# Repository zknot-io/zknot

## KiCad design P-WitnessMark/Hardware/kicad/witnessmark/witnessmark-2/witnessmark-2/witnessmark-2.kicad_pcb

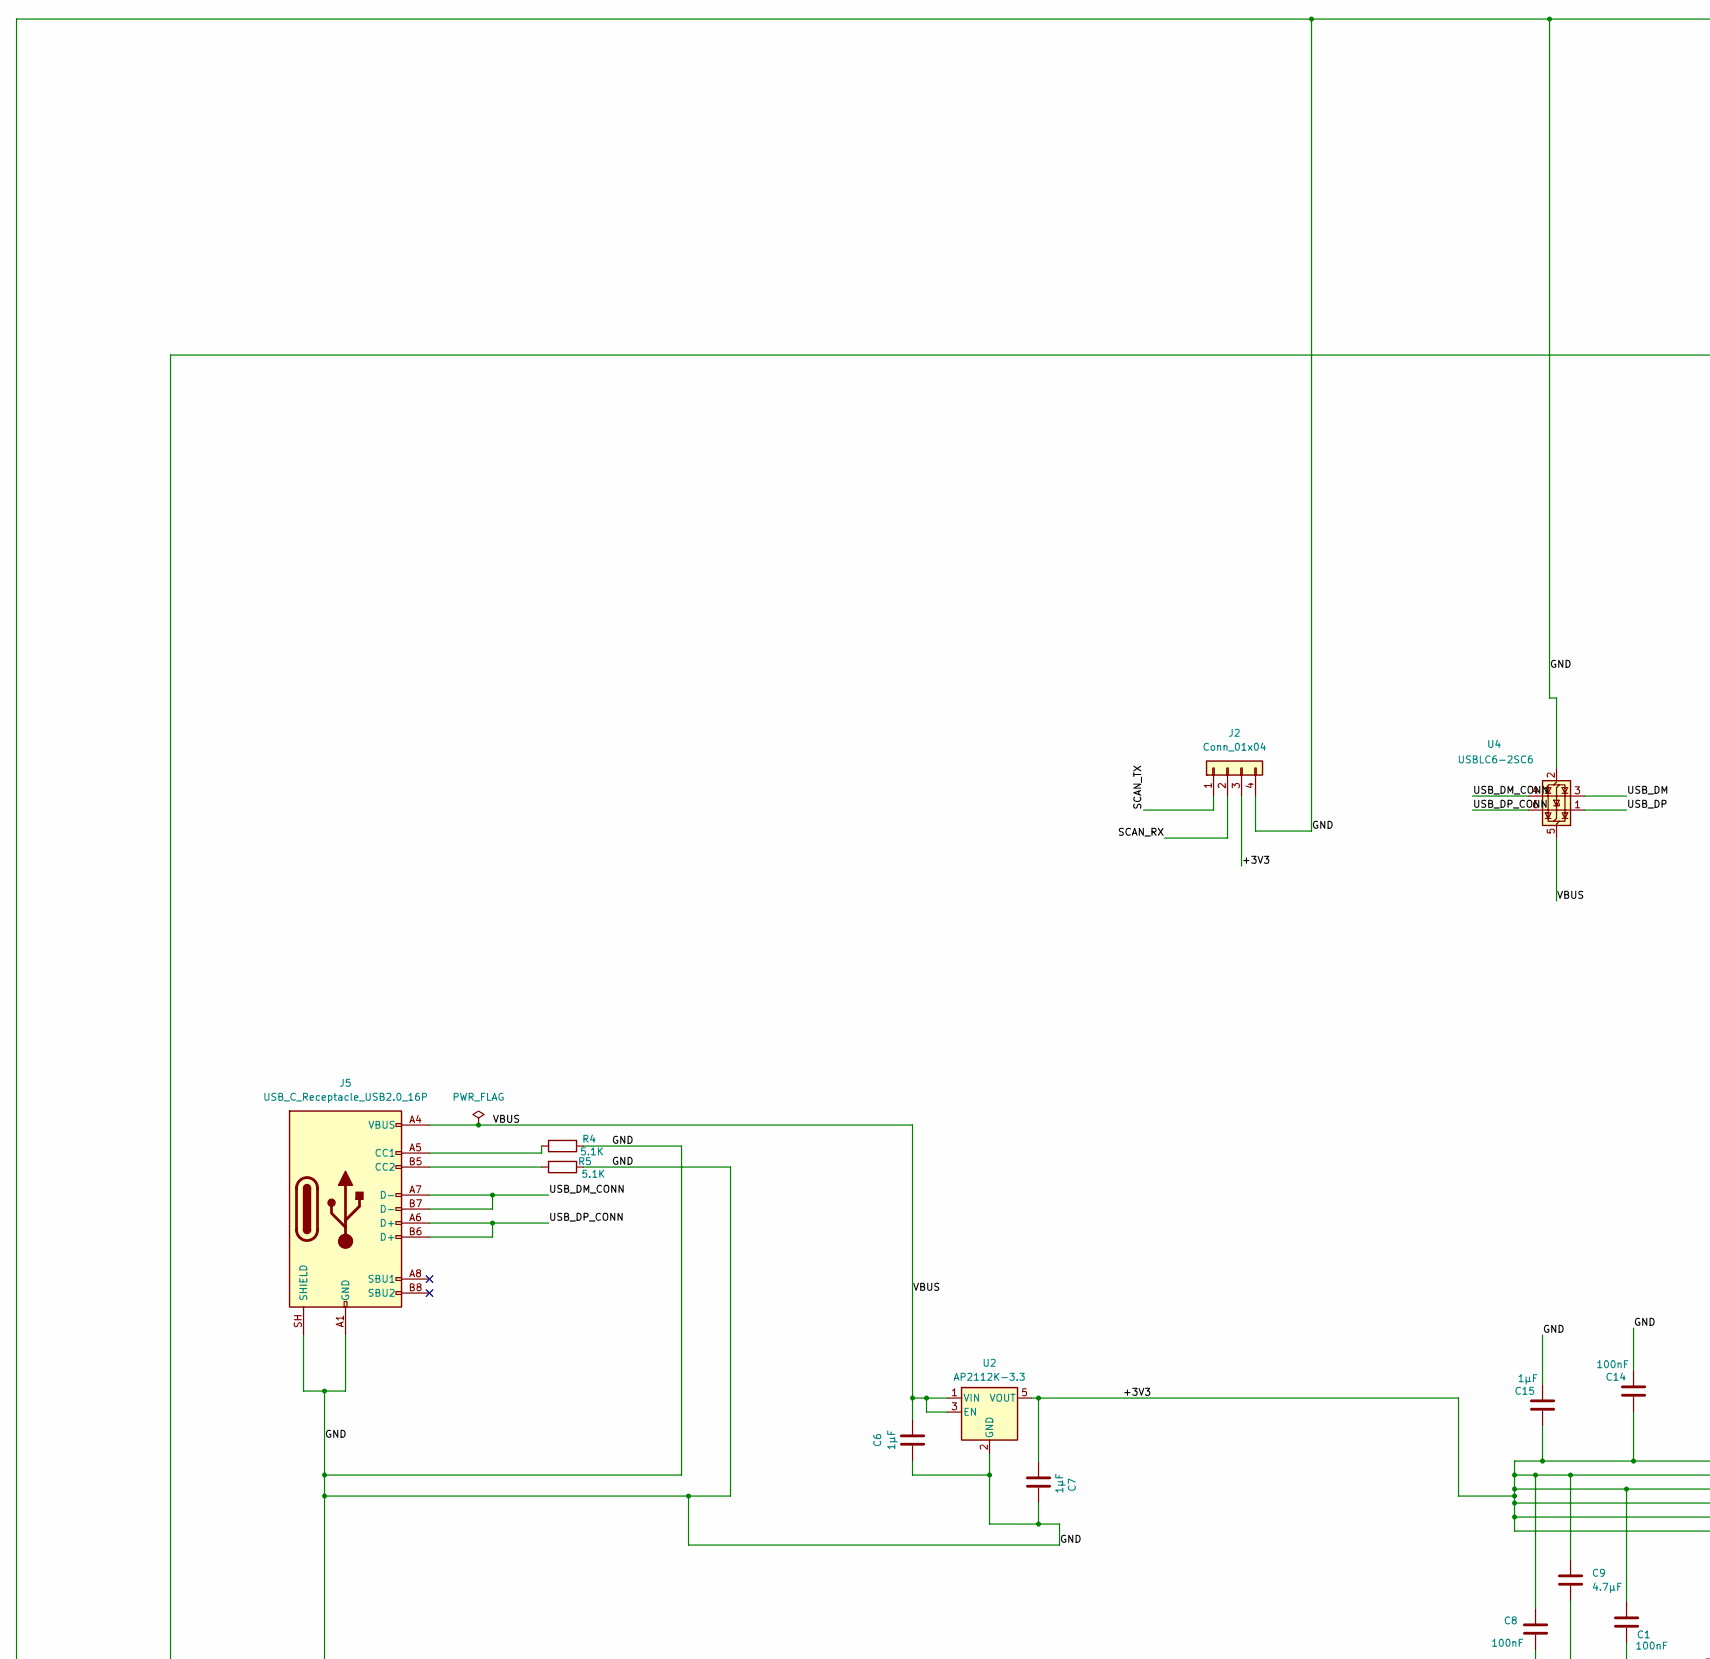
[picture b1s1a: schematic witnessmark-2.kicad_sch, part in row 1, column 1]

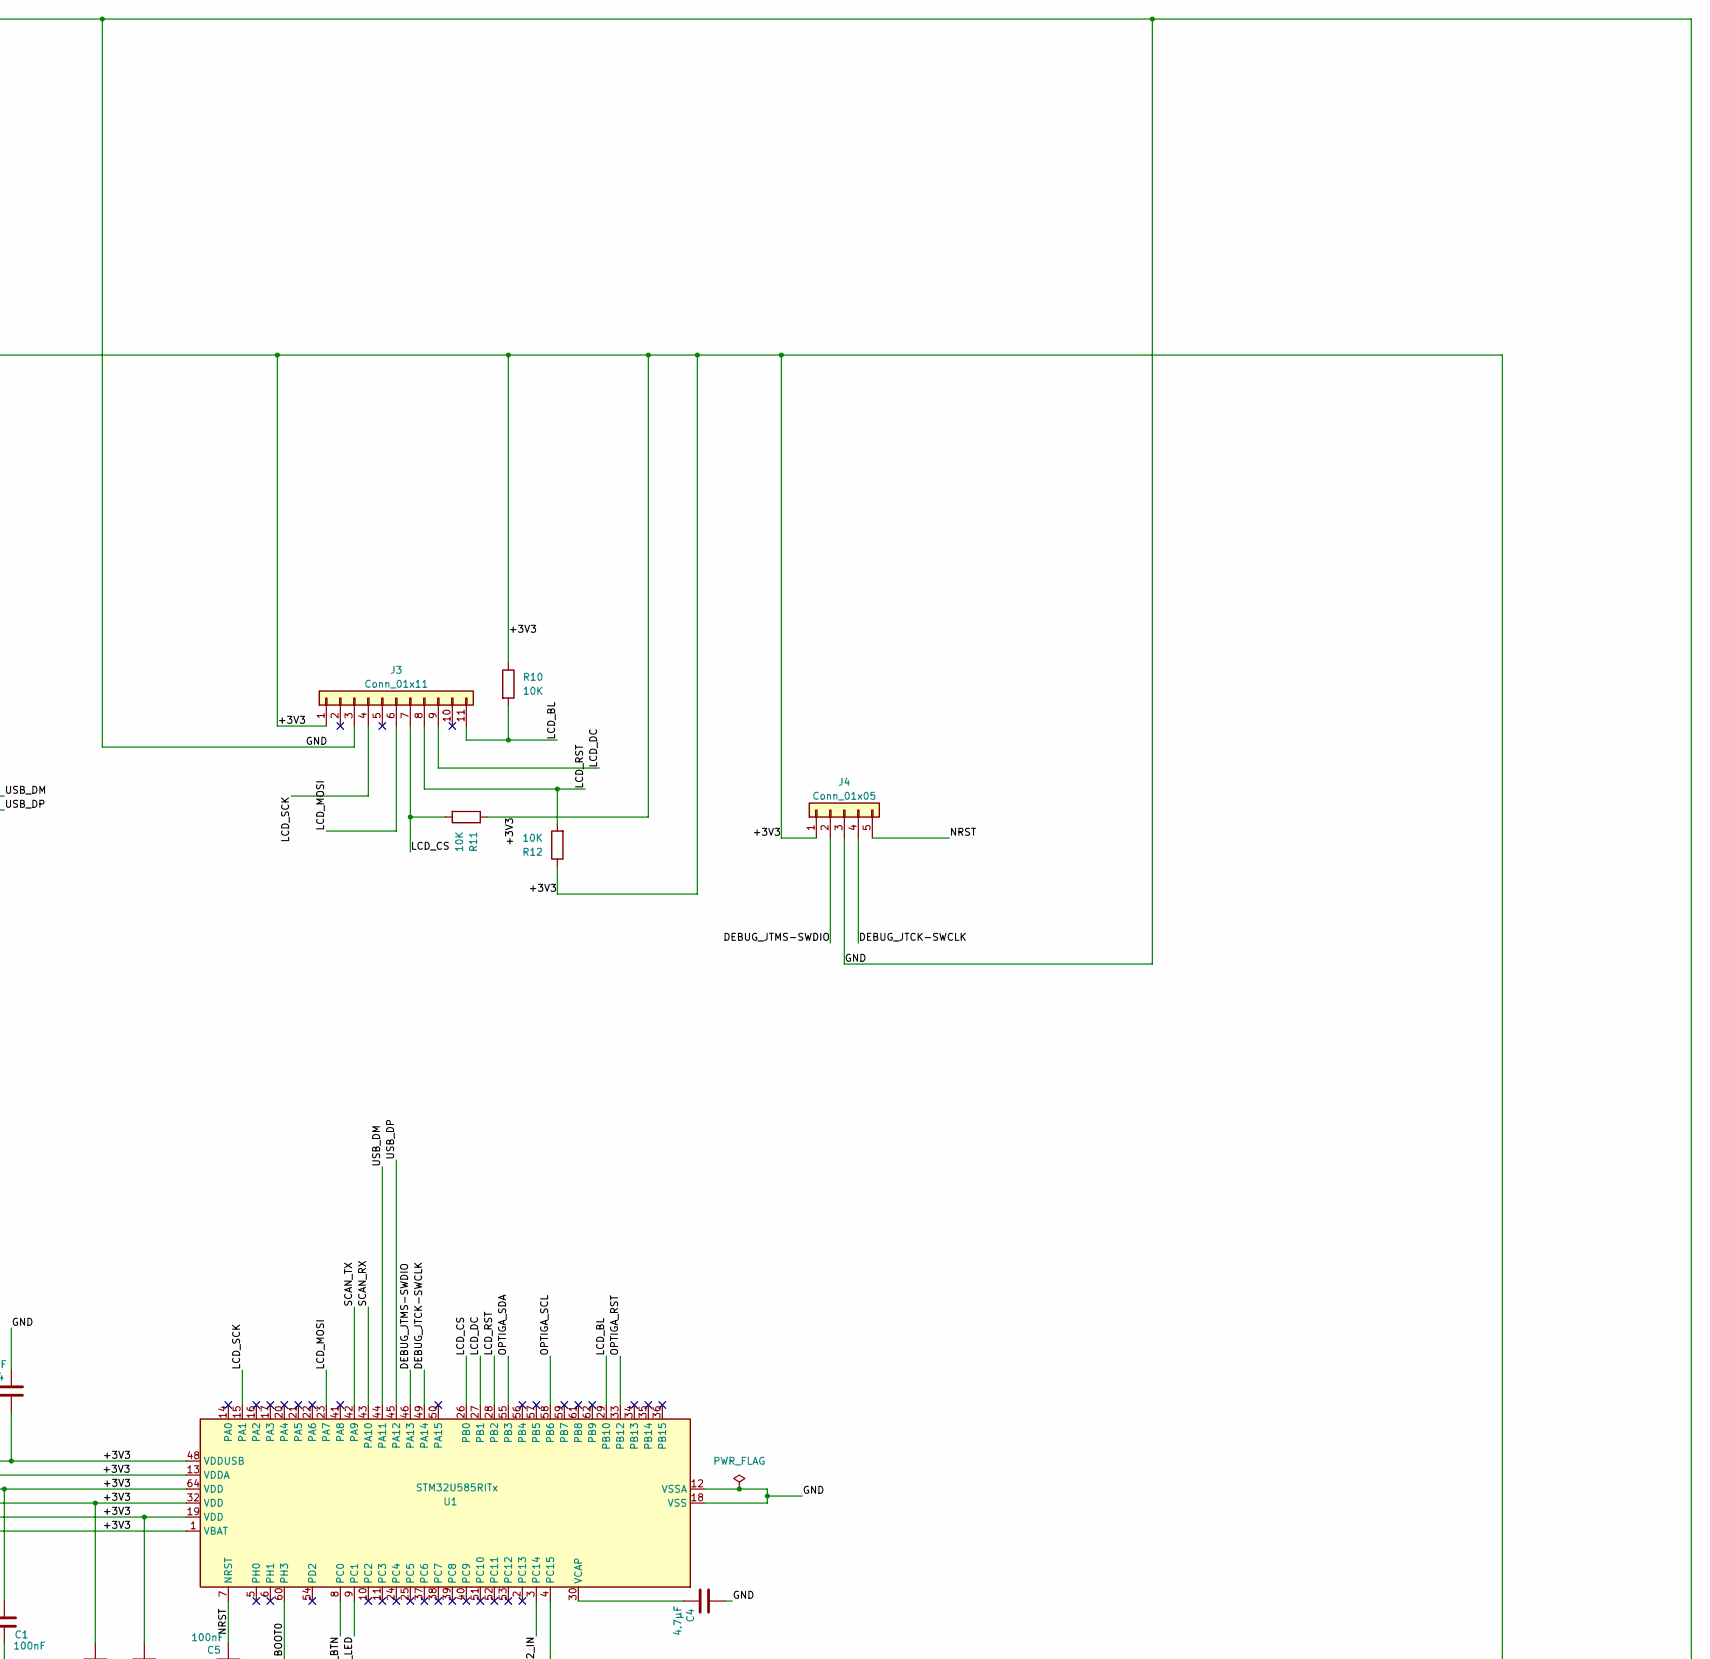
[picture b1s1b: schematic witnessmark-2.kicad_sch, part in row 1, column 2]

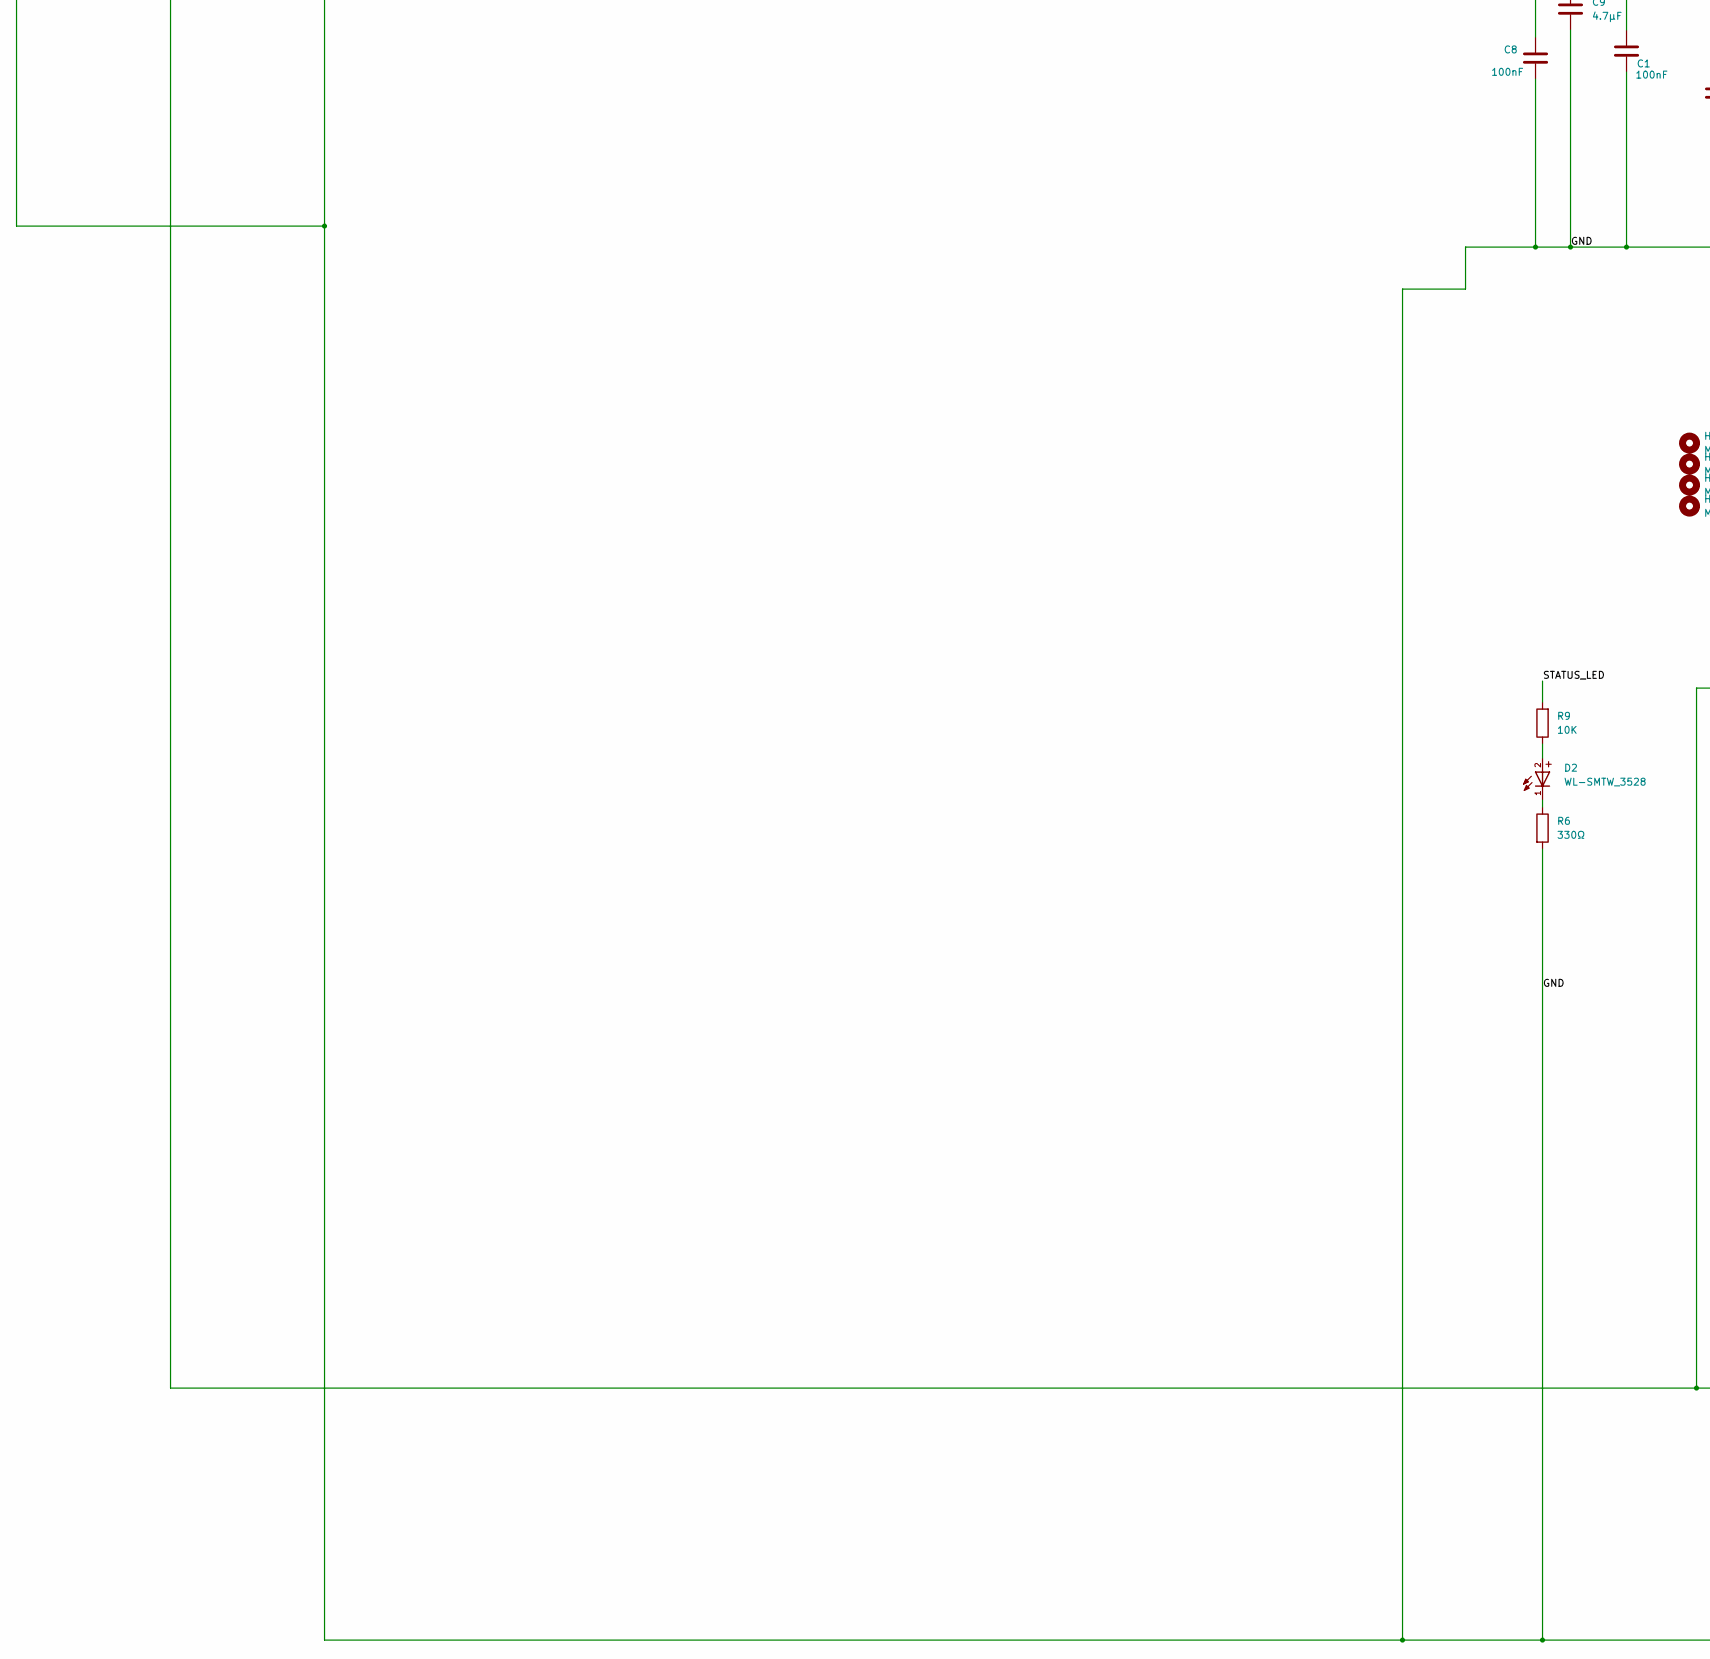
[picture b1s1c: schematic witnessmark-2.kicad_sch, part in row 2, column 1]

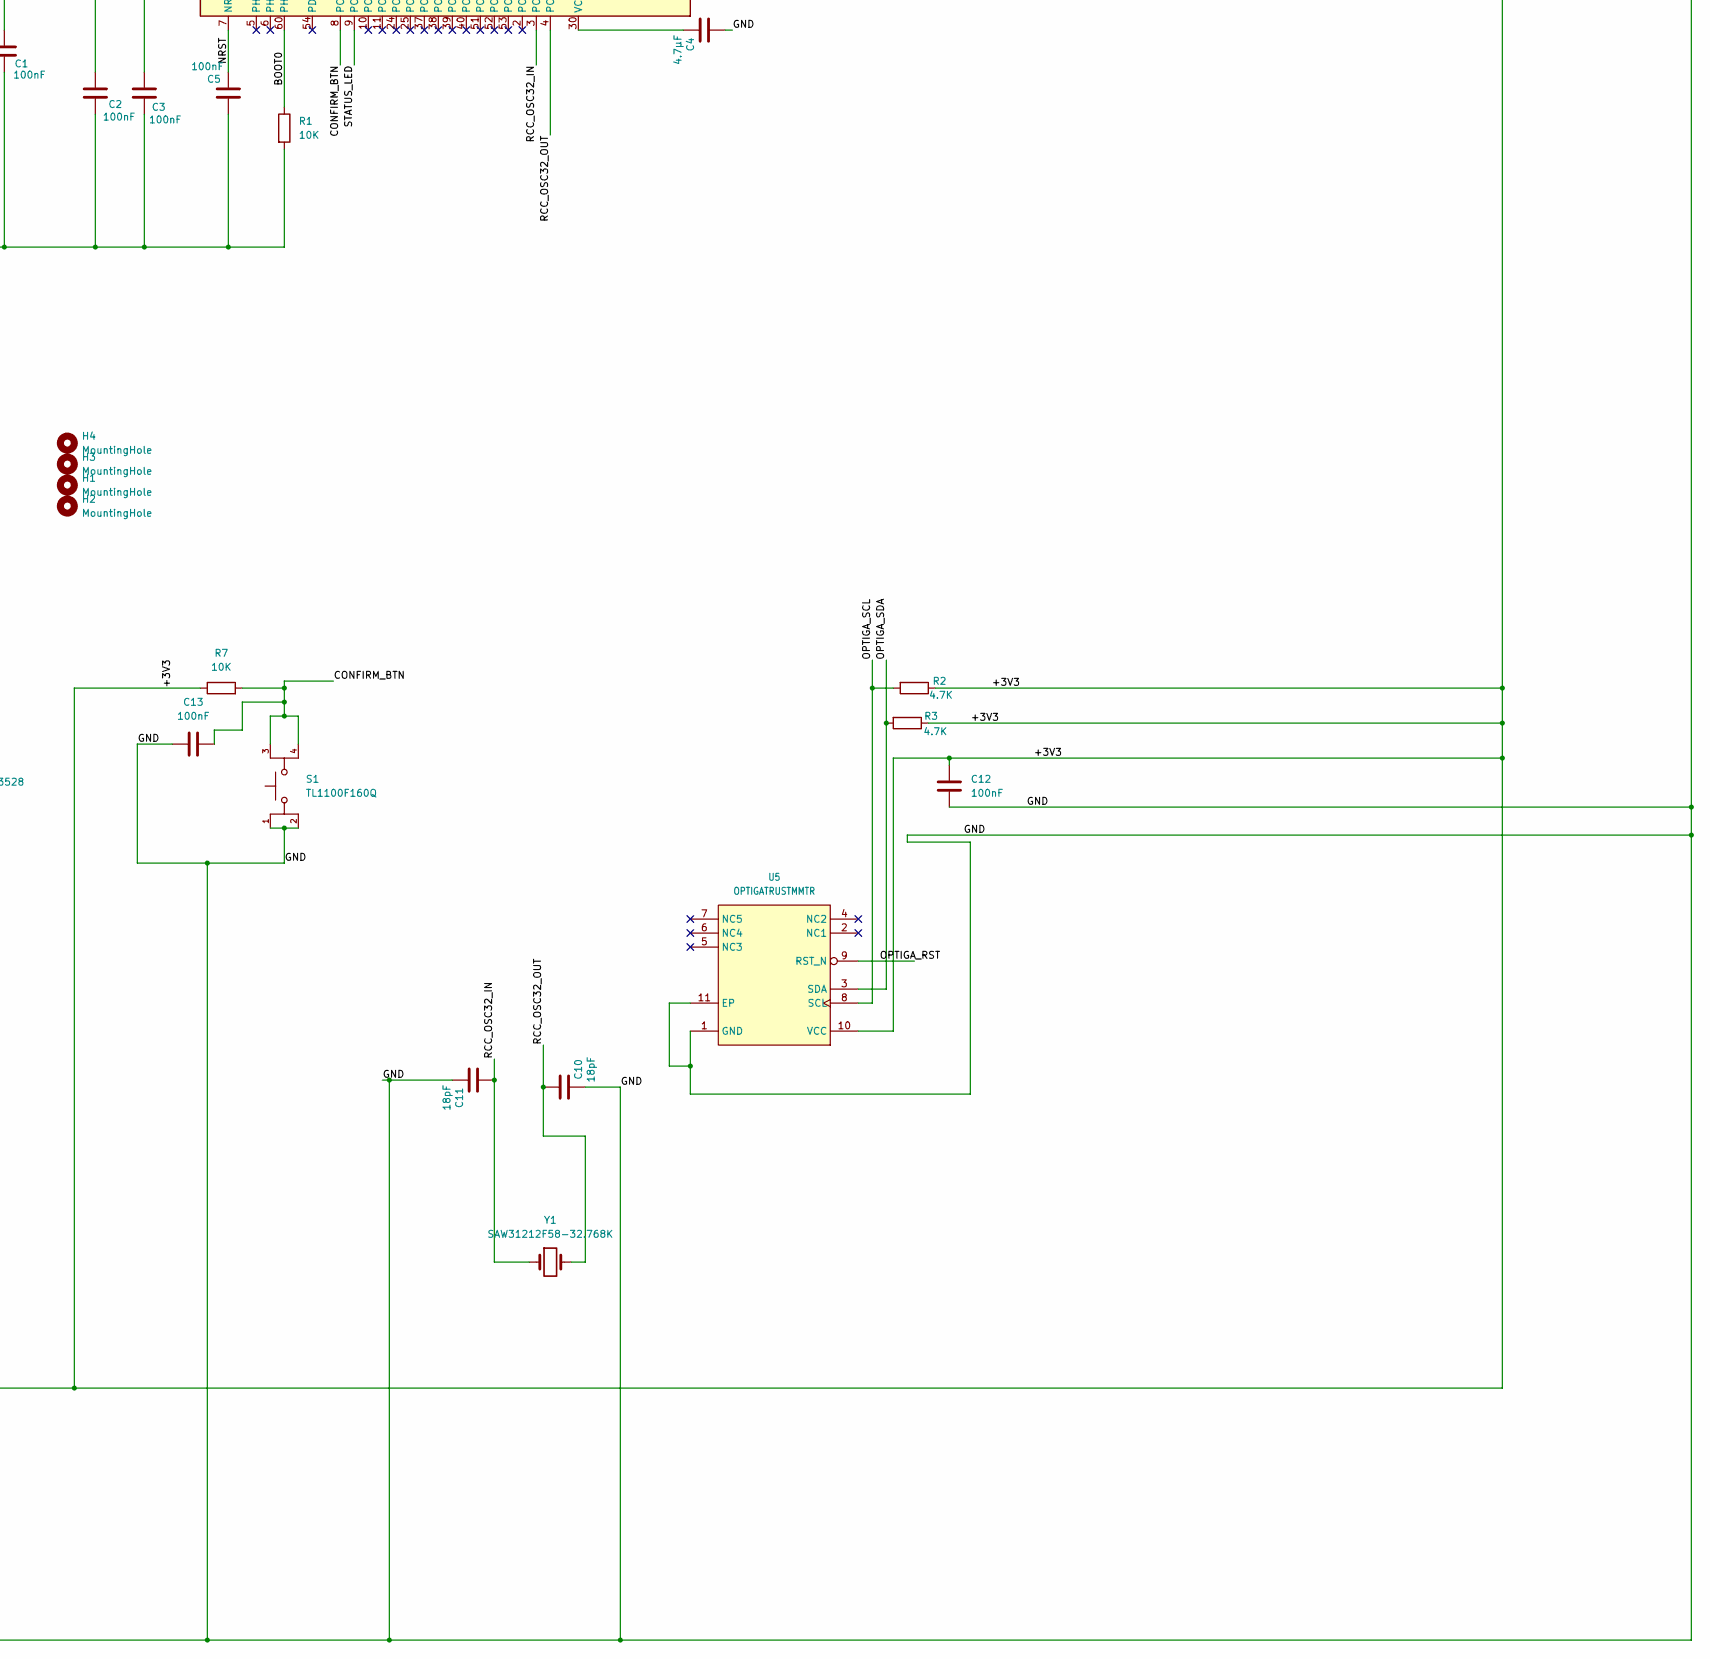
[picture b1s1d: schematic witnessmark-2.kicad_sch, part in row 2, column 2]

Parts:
C1, C2, C3, C5, C8, C12, C13, C14: 100nF; C_0603_1608Metric
C4, C9: 4.7µF; C_0603_1608Metric
C6, C7, C15: 1µF; C_0603_1608Metric
C10, C11: 18pF; C_0603_1608Metric
D2: WL-SMTW_3528
H1, H2, H3, H4: MountingHole; MountingHole_2.5mm_Pad
J2: Conn_01x04; PinHeader_1x04_P2.54mm_Vertical
J3: Conn_01x11; PinHeader_1x11_P2.54mm_Vertical
J4: Conn_01x05; PinSocket_1x05_P2.54mm_Vertical
J5: USB_C_Receptacle_USB2.0_16P; USB_C_Receptacle_GCT_USB4105-xx-A_16P_TopMnt_Horizontal
R1, R7, R9, R10, R11, R12: 10K; R_0603_1608Metric
R2, R3: 4.7K; R_0603_1608Metric
R4, R5: 5.1K; R_0603_1608Metric
R6: 330Ω; R_0603_1608Metric
S1: TL1100F160Q; SW_TL1100F160Q; PARTREV D
U1: STM32U585RITx; LQFP-64_10x10mm_P0.5mm
U2: AP2112K-3.3; SOT-23-5
U4: USBLC6-2SC6; SOT-23-6
U5: OPTIGATRUSTMMTR; SON50P300X300X60-11N-V
Y1: SAW31212F58-32.768K; Crystal_SMD_3215-2Pin_3.2x1.5mm

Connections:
/+3V3: C1.1, C2.1, C3.1, C7.2, C8.2, C9.2, C12.1, C14.1, C15.1, J2.3, J3.1, J4.1, R2.1, R3.1, R7.1, R10.1, R11.1, R12.1, U1.1 (VBAT), U1.13 (VDDA), U1.19 (VDD), U1.32 (VDD), U1.48 (VDDUSB), U1.64 (VDD), U2.5 (VOUT), U5.10 (VCC)
/BOOT0: R1.1, U1.60 (PH3)
/CONFIRM_BTN: C13.2, R7.2, S1.3, S1.4, U1.8 (PC0)
/DEBUG_JTCK-SWCLK: J4.4, U1.49 (PA14)
/DEBUG_JTMS-SWDIO: J4.2, U1.46 (PA13)
/GND: C1.2, C2.2, C3.2, C4.1, C5.1, C6.1, C7.1, C8.1, C9.1, C10.2, C11.2, C12.2, C13.1, C14.2, C15.2, J2.4, J3.3, J4.3, J5.A1 (GND), J5.A12 (GND), J5.B1 (GND), J5.B12 (GND), J5.SH (SHIELD), R1.2, R4.1, R5.1, R6.2, S1.1, S1.2, U1.12 (VSSA), U1.18 (VSS), U1.31 (VSS), U1.47 (VSS), U1.63 (VSS), U2.2 (GND), U4.2 (GND), U5.1 (GND), U5.11 (EP)
/LCD_BL: J3.11, R10.2, U1.29 (PB10)
/LCD_CS: J3.7, R11.2, U1.26 (PB0)
/LCD_DC: J3.9, U1.27 (PB1)
/LCD_MOSI: J3.6, U1.23 (PA7)
/LCD_RST: J3.8, R12.2, U1.28 (PB2)
/LCD_SCK: J3.4, U1.15 (PA1)
/NRST: C5.2, J4.5, U1.7 (NRST)
/OPTIGA_RST: U1.33 (PB12), U5.9 (RST_N)
/OPTIGA_SCL: R2.2, U1.58 (PB6), U5.8 (SCL)
/OPTIGA_SDA: R3.2, U1.55 (PB3), U5.3 (SDA)
/RCC_OSC32_IN: C11.1, U1.3 (PC14), Y1.1
/RCC_OSC32_OUT: C10.1, U1.4 (PC15), Y1.2
/SCAN_RX: J2.2, U1.43 (PA10)
/SCAN_TX: J2.1, U1.42 (PA9)
/STATUS_LED: R9.2, U1.9 (PC1)
/USB_DM: U1.44 (PA11), U4.3 (I/O2)
/USB_DM_CONN: J5.A7 (D-), J5.B7 (D-), U4.4 (I/O2)
/USB_DP: U1.45 (PA12), U4.1 (I/O1)
/USB_DP_CONN: J5.A6 (D+), J5.B6 (D+), U4.6 (I/O1)
/VBUS: C6.2, J5.A4 (VBUS), J5.A9 (VBUS), J5.B4 (VBUS), J5.B9 (VBUS), U2.1 (VIN), U2.3 (EN), U4.5 (VBUS)
unnamed: D2.1, R6.1
unnamed: D2.2, R9.1
unnamed: J5.A5 (CC1), R4.2
unnamed: J5.B5 (CC2), R5.2
unnamed: C4.2, U1.30 (VCAP)

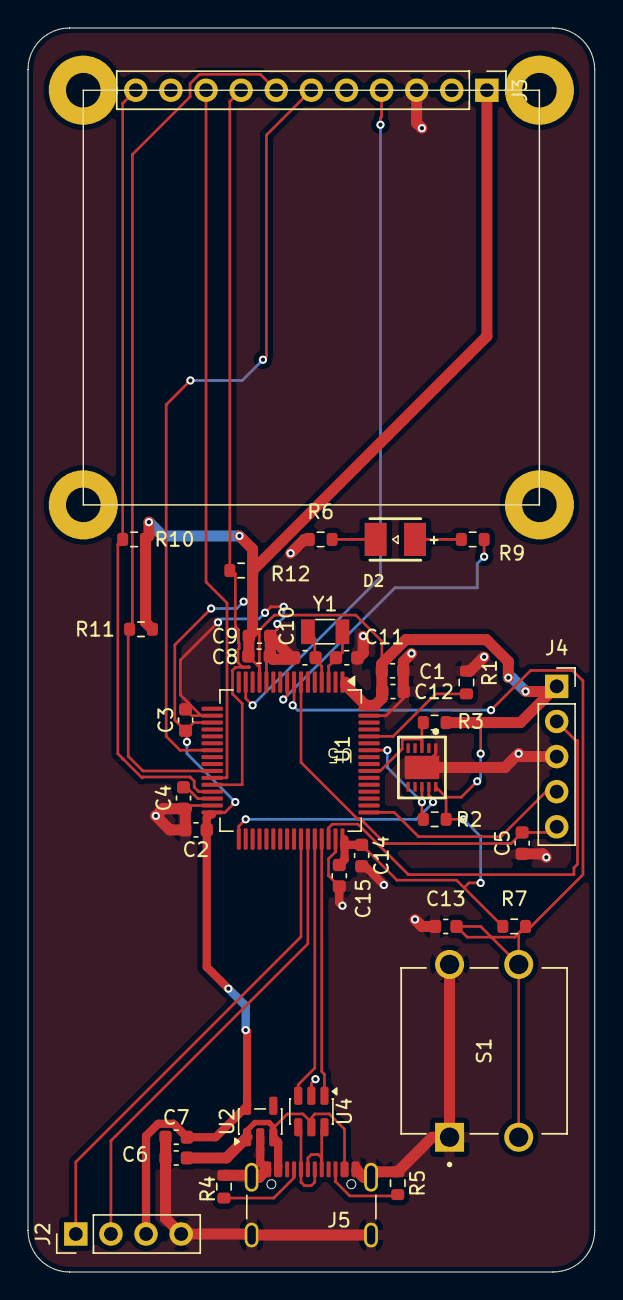
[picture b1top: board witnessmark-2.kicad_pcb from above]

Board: 2 copper layers, 41.0 x 90.0 mm, 41 parts (0 on the bottom side), 31 nets.

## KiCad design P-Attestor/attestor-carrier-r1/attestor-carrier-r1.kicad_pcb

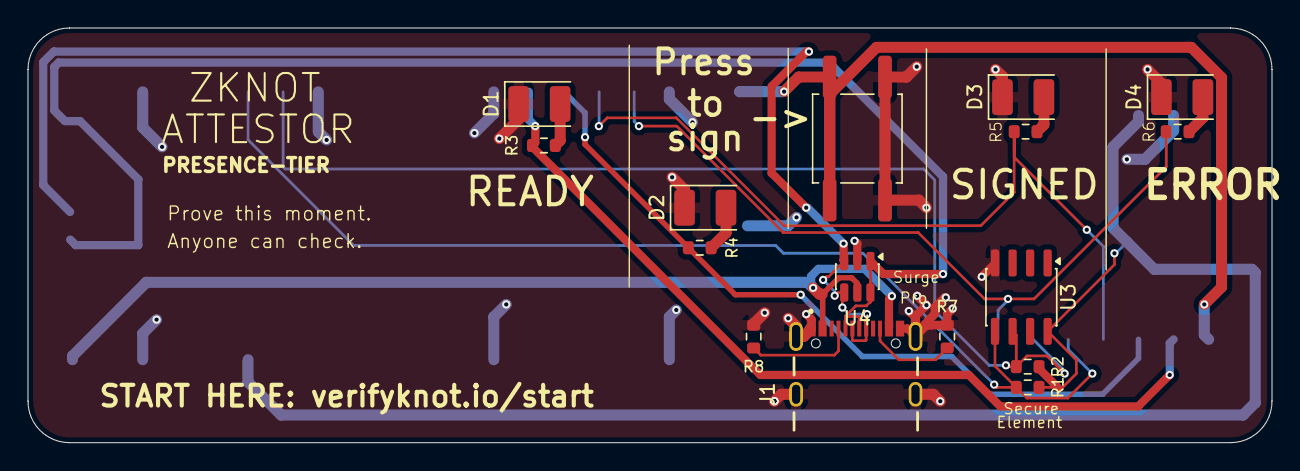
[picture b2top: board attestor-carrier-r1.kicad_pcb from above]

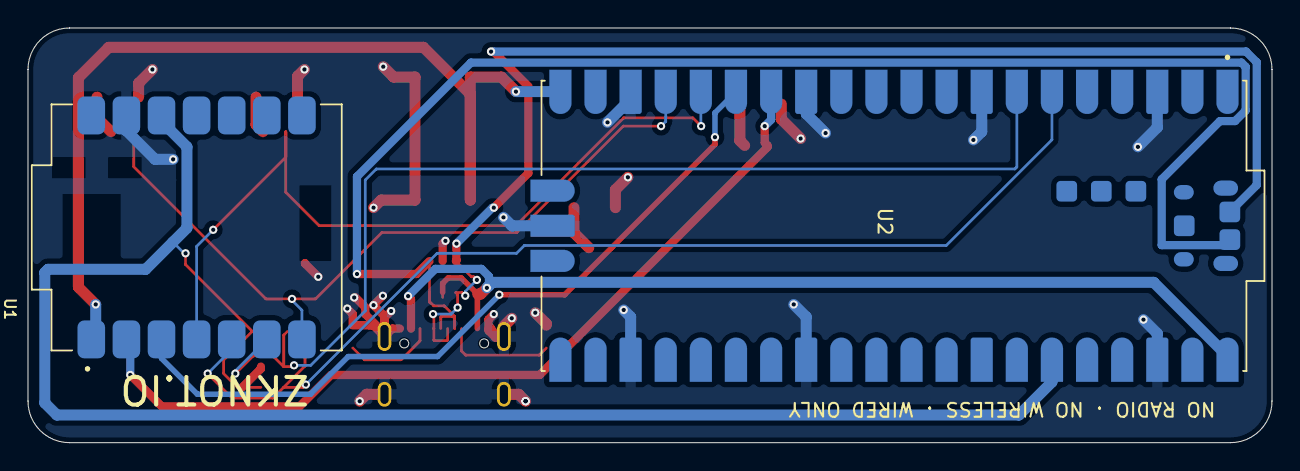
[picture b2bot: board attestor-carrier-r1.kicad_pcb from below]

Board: 2 copper layers, 90.0 x 30.0 mm, 18 parts (2 on the bottom side), 18 nets.

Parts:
D1: Green; LED_PLCC-2_3.4x3.0mm_KA
D2: Yellow; LED_PLCC-2_3.4x3.0mm_KA
D3: Blue; LED_PLCC-2_3.4x3.0mm_KA
D4: Red; LED_PLCC-2_3.4x3.0mm_KA
J1: USB4105-GF-A
R1, R2: 4.7k; R_0603_1608Metric
R3, R4, R5, R6: 330Ω; R_0603_1608Metric
R7, R8: 5.1 kΩ; R_0603_1608Metric
SW1: SW_Push; SW_Push_1P1T_NO_CK_KSC6xxG
U1: 102010428; MODULE_102010428
U2: SC0915; MODULE_SC0915
U3: ATECC608B-SSHDA; SOIC-8_3.9x4.9mm_P1.27mm
U4: USBLC6-2SC6; SOT-23-6

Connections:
/3V3: R1.1, R2.1, U1.12 (3V3), U2.35 (ADC_VREF), U3.8 (VCC)
/BTN: SW1.1, U1.1 (P26/A0/D0), U2.20 (GP15)
/LED_B: R5.2, U1.4 (P29/A3/D3), U2.16 (GP12)
/LED_G: R3.2, U1.2 (P27/A1/D1), U2.14 (GP10)
/LED_R: R6.2, U1.7 (P0//TX/D6), U2.17 (GP13)
/LED_Y: R4.2, U1.3 (P28/A2/D2), U2.15 (GP11)
/SCL: R2.2, U1.6 (P7/SCL/D5), U2.7 (GP5), U3.6 (SCL)
/SDA: R1.2, U1.5 (P6/SDA/D4), U2.6 (GP4), U3.5 (SDA)
/USB_DM: J1.A7 (DN1), J1.B7 (DN2), U2.TP2 (TP2_USB_DM), U4.1 (I/O1), U4.6 (I/O1)
/USB_DP: J1.A6 (DP1), J1.B6 (DP2), U2.TP3 (TP3_USB_DP), U4.3 (I/O2), U4.4 (I/O2)
/VBUS: J1.A4_B9 (VBUS), J1.B4_A9 (VBUS__1), U2.40 (VBUS), U4.5 (VBUS)
GND: D1.1 (K), D2.1 (K), D3.1 (K), D4.1 (K), J1.A1_B12 (GND), J1.B1_A12 (GND__1), J1.SH1 (SHELL_GND), J1.SH2 (SHELL_GND__1), J1.SH3 (SHELL_GND__2), J1.SH4 (SHELL_GND__3), R7.2, R8.1, SW1.2, U1.13 (GND), U2.3 (GND), U2.8 (GND), U2.13 (GND), U2.18 (GND), U2.23 (GND), U2.28 (GND), U2.38 (GND), U2.D2 (GND), U3.4 (GND), U4.2 (GND)
unnamed: D1.2 (A), R3.1
unnamed: D2.2 (A), R4.1
unnamed: D3.2 (A), R5.1
unnamed: D4.2 (A), R6.1
unnamed: J1.A5 (CC1), R8.2
unnamed: J1.B5 (CC2), R7.1

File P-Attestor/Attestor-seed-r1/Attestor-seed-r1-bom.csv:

"Reference","Value","Footprint","QUANTITY","DNP","MPN","Manufacturer"
"D1","Green","attestor:WL-SMTW_3528","1","","",""
"D2","Yellow","attestor:WL-SMTW_3528","1","","",""
"D3","Blue","attestor:WL-SMTW_3528","1","","",""
"D4","Red","attestor:WL-SMTW_3528","1","","",""
"R1,R2","4.7k","Resistor_SMD:R_0603_1608Metric","2","","",""
"R3-R6","330Ω","Resistor_SMD:R_0603_1608Metric","4","","",""
"S1","TL1100F160Q","attestor:SW_TL1100F160Q","1","","","E-Switch"
"U1","102010428","attestor:MODULE_102010428","1","","","Seeedstudio"
"U3","ATECC608B-SSHDA","Package_SO:SOIC-8_3.9x4.9mm_P1.27mm","1","","",""

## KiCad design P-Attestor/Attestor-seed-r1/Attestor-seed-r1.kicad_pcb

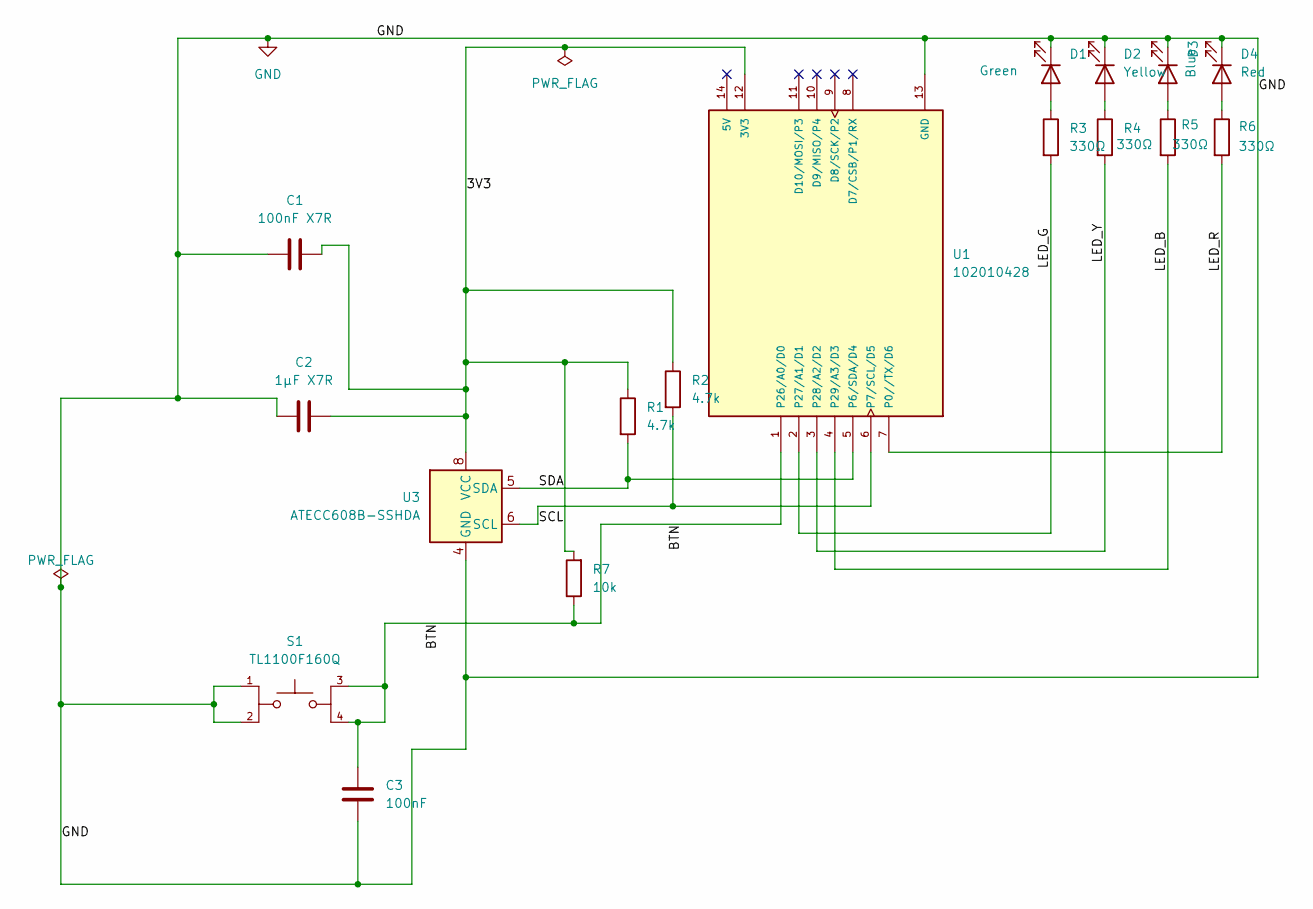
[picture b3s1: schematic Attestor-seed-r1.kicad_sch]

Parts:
C1: 100nF X7R; C_0603_1608Metric
C2: 1µF X7R; C_0603_1608Metric
C3: 100nF; C_0603_1608Metric
D1: Green; WL-SMTW_3528
D2: Yellow; WL-SMTW_3528
D3: Blue; WL-SMTW_3528
D4: Red; WL-SMTW_3528
R1, R2: 4.7k; R_0603_1608Metric
R3, R4, R5, R6: 330Ω; R_0603_1608Metric
R7: 10k; R_0603_1608Metric
S1: TL1100F160Q; SW_TL1100F160Q; PARTREV D
U1: 102010428; MODULE_102010428; PARTREV 1.3
U3: ATECC608B-SSHDA; SOIC-8_3.9x4.9mm_P1.27mm

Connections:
/3V3: C1.2, C2.2, R1.1, R2.1, R7.2, U1.12 (3V3), U3.8 (VCC)
/BTN: C3.2, R7.1, S1.3, S1.4, U1.1 (P26/A0/D0)
/LED_B: R5.2, U1.4 (P29/A3/D3)
/LED_G: R3.2, U1.2 (P27/A1/D1)
/LED_R: R6.2, U1.7 (P0//TX/D6)
/LED_Y: R4.2, U1.3 (P28/A2/D2)
/SCL: R2.2, U1.6 (P7/SCL/D5), U3.6 (SCL)
/SDA: R1.2, U1.5 (P6/SDA/D4), U3.5 (SDA)
GND: C1.1, C2.1, C3.1, D1.1 (K), D2.1 (K), D3.1 (K), D4.1 (K), S1.1, S1.2, U1.13 (GND), U3.4 (GND)
unnamed: D1.2 (A), R3.1
unnamed: D2.2 (A), R4.1
unnamed: D3.2 (A), R5.1
unnamed: D4.2 (A), R6.1

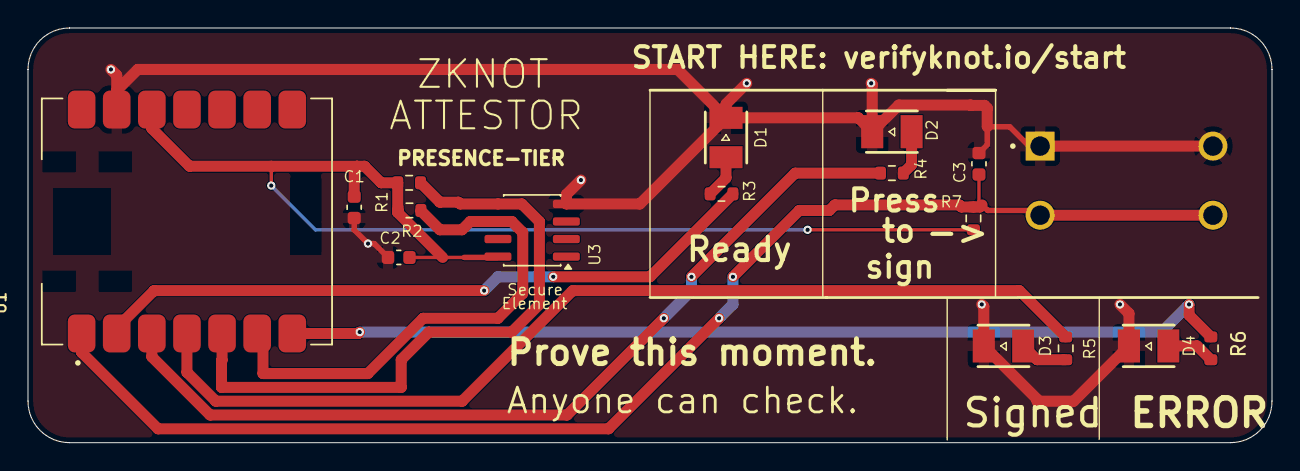
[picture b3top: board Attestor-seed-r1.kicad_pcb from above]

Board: 2 copper layers, 90.0 x 30.0 mm, 17 parts (0 on the bottom side), 13 nets.

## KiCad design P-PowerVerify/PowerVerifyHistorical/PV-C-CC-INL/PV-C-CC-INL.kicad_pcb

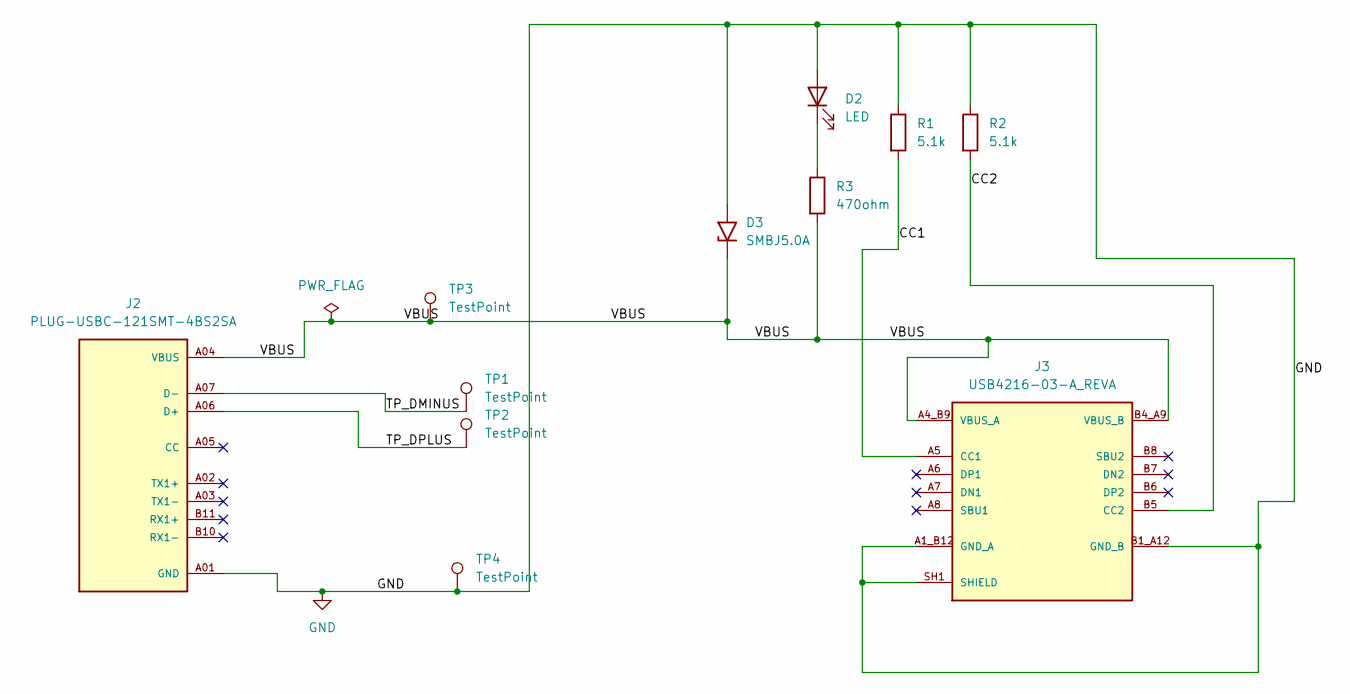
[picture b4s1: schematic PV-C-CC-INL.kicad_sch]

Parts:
D2: LED; LED_0603_1608Metric
D3: SMBJ5.0A; D_SMB
J2: PLUG-USBC-121SMT-4BS2SA; GLOBTEK_PLUG-USBC-121SMT-4BS2SA; PARTREV A1; DigiKey_Part_Number 1939-PLUG-USBC-121SMT-4BS2SACT-ND
J3: USB4216-03-A_REVA; GCT_USB4216-03-A_REVA; PARTREV A
R1, R2: 5.1k; R_0402_1005Metric
R3: 470ohm; R_0402_1005Metric
TP1, TP2, TP3, TP4: TestPoint; TestPoint_Pad_D1.5mm

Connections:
/CC1: J3.A5 (CC1), R1.2
/CC2: J3.B5 (CC2), R2.2
/TP_DMINUS: J2.A07 (D-), TP1.1
/TP_DPLUS: J2.A06 (D+), TP2.1
GND: D2.2 (A), D3.2 (A2), J2.A01 (GND), J2.A12 (GND), J2.B12 (GND), J2.G1 (GND), J2.G2 (GND), J3.A1_B12 (GND_A), J3.B1_A12 (GND_B), J3.SH1 (SHIELD), J3.SH2 (SHIELD), J3.SH3 (SHIELD), J3.SH4 (SHIELD), R1.1, R2.1, TP4.1
unnamed: D2.1 (K), R3.1
VBUS: D3.1 (A1), J2.A04 (VBUS), J2.B09 (VBUS), J3.A4_B9 (VBUS_A), J3.B4_A9 (VBUS_B), R3.2, TP3.1

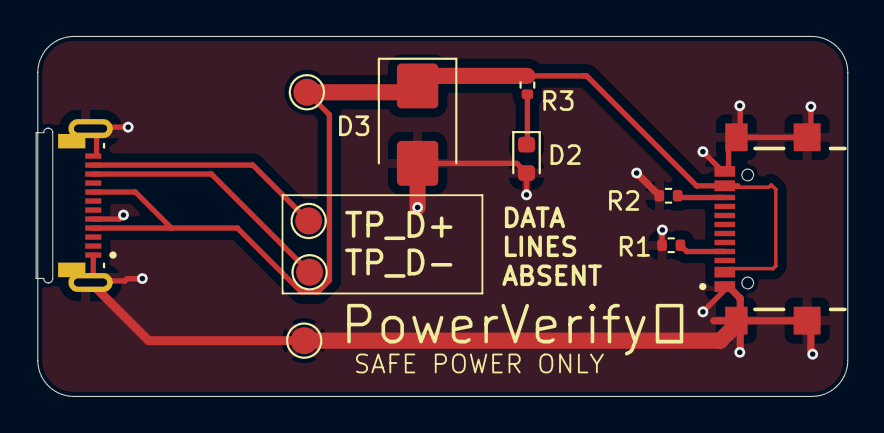
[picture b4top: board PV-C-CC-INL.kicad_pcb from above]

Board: 2 copper layers, 45.0 x 20.0 mm, 11 parts (0 on the bottom side), 7 nets.

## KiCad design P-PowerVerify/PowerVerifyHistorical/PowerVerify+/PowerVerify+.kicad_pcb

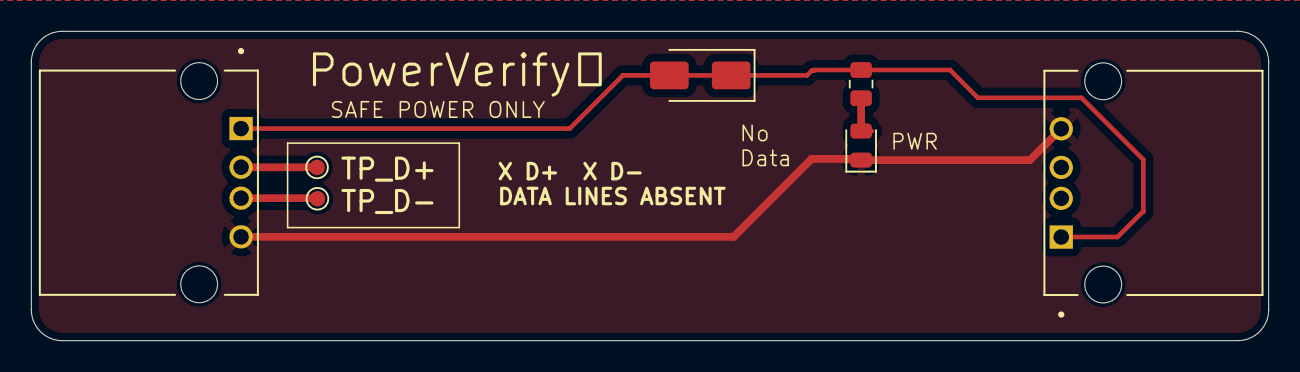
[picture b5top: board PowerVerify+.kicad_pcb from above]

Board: 2 copper layers, 80.0 x 20.0 mm, 7 parts (0 on the bottom side), 3 nets.

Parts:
D1: LED GREEN; LED_0805_2012Metric
D3: D_TVS; D_SMA
J1, J2: USB_A; OST_USB-A1HSW6
R3: 1k; R_0805_2012Metric
TP1: TP_DPLUS; TestPoint_Pad_D1.0mm
TP2: TP_DMINUS; TestPoint_Pad_D1.0mm

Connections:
GND: D1.1 (K), J1.4 (GND), J2.4 (GND)
unnamed: D1.2 (A), R3.1
VBUS: D3.1 (A1), D3.2 (A2), J1.1 (VBUS), J2.1 (VBUS), R3.2

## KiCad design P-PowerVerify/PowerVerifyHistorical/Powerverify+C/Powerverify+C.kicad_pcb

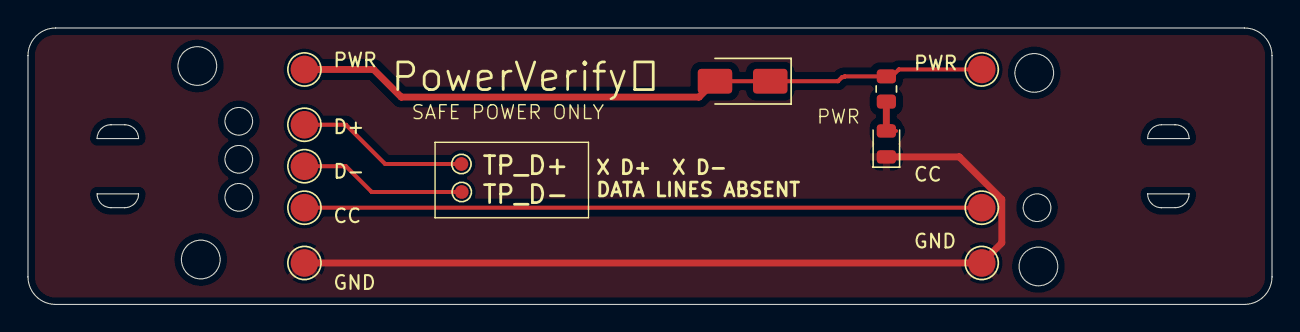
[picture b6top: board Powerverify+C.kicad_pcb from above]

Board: 2 copper layers, 90.0 x 20.0 mm, 13 parts (0 on the bottom side), 4 nets.

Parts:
D1: LED GREEN; LED_0805_2012Metric
D3: D_TVS; D_SMA
R3: 1k; R_0805_2012Metric
TP1: TP_DPLUS; TestPoint_Pad_D1.0mm
TP2: TP_DMINUS; TestPoint_Pad_D1.0mm
TP3, TP4, TP5, TP6, TP7, TP8, TP9, TP10: TestPoint; TestPoint_Pad_D2.0mm

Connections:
GND: D1.1 (K), TP7.1, TP8.1
unnamed: D1.2 (A), R3.1
unnamed: TP4.1, TP9.1
VBUS: D3.1 (A1), D3.2 (A2), R3.2, TP3.1, TP10.1
